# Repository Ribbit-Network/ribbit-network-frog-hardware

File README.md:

# Ribbit Network Frog Sensor
<!-- ALL-CONTRIBUTORS-BADGE:START - Do not remove or modify this section -->

<!-- ALL-CONTRIBUTORS-BADGE:END -->
[This project will create the world's largest Greenhouse Gas Emissions dataset that will empower anyone to join in the work on climate and provide informed data for climate action.](https://ribbitnetwork.org/)

Ribbit Network is a large network of open-source, low-cost, Greenhouse Gas (CO2 and hopefully other gasses in the future) Detection Sensors. These sensor units will be sold by the Ribbit Network and will upload their data to the cloud, creating the world's most complete Greenhouse Gas dataset.

This repository contains the design files, software, documentation, and assembly instructions for the Frog Sensor.

## Frog Sensors
Our “Frogs” are tiny sensors that you can build and deploy at your own home! It’s a small, 
open-source device that measures the amount of CO2 in the air using a tiny laser.
It's easy to set up and will constantly record valuable scientific data on our climate.

Frogs are one of the species that are most affected by climate change! 
Just like our sensors, they ribbit to one another to create a powerful network 
of data about the environment.

## Build a Frog!
We encourage you to jump in and build your own Frog Sensor! It's recommended
to build a V4 Frog and the instructions from this repo are rendered into a nice webpage at the link below:

[Build a Frog Sensor!](https://ribbit-network.github.io/ribbit-network-frog-hardware/)

There have been four major versions of the Frog Sensor to date. We currently recommend building version 4 of the Frog and this repo contains the files and instructions relevant to V4.

* Frog Sensor Version 4 - This version of the sensor is based on an esp32 microcontroller.
* [Frog Sensor Version 3](https://github.com/Ribbit-Network/ribbit-network-frog-hardware/tree/hw_v3) - This version is based on a Raspberry Pi CM4 and includes a fully 3D printed enclosure.
* [Frog Sensor Version 2](https://github.com/Ribbit-Network/ribbit-network-frog-hardware/tree/hw_v2) - This version is based on a Beaglebone black and includes a fully 3D printed enclosure.
* [Frog Sensor Version 1](https://github.com/Ribbit-Network/ribbit-network-frog-hardware/tree/hw_v1) - This version was based on the Raspberry Pi and included an off-the-shelf enclosure

See each folder linked above for the relevant design files, CAD, and assembly instructions!

## Need Help?
[If you are not sure where to start or just want to chat join our developer slack here.](https://join.slack.com/t/ribbitnetworkgroup/shared_invite/zt-2vxvbo7ld-S36SgfDiev~ZQ2zvp03FOg). You can also [start a discussion](https://github.com/Ribbit-Network/ribbit-network-frog-sensor/discussions) right here in Github.

# View the Data!
The first prototype sensors are up and running! [Here is some real data from our sensor network!](https://dashboard.ribbitnetwork.org/) (Note this dashboard is still experimental and may be down occasionally).

[See more about the cloud database here.](https://github.com/Ribbit-Network/ribbit-network-dashboard)

## Questions?
[Check out the Frequently Asked Questions section.](https://github.com/Ribbit-Network/ribbit-network-faq) If you don't see your question, let us know either in a Github Discussion or via chat.

## Ribbit Frog V4
This is the hardware repository that contains all the design files for the physical assembly of the Frog Sensor.

## Bill of Materials (Parts List)
The hardware [Bill of Materials is located here.](ribbit_network_frog_sensor_bom.csv)

## Mechanical CAD Files
The mechanical design files are hosted on Onshape. Onshape is available to use for free with public assemblies and you can create a copy of the assembly for any edits you would like to make.

[Link to Onshape Assembly](https://cad.onshape.com/documents/b3e6eeabf50d585d20f25fc6/w/a4a82302d129f025f23b244a/e/c221edb50cd05a98d22970e2?renderMode=0&uiState=64a86ef7086f6a55cf1984e7)

## Electronics Block Diagram

The diagram above can be edited with drawio or with the awesome [Draw.io Visual Studio Code Plugin](https://marketplace.visualstudio.com/items?itemName=hediet.vscode-drawio)

## Get Involved
Are you interested in getting more involved or leading an effort in the Ribbit Network project? We are recruiting for additional members to join the Core Team. [See the Open Roles and descriptions here.](https://ribbitnetwork.notion.site/Core-Team-Role-Postings-105df298e0634f179f8f063c01708069).

## Contributing
See the [Issues](https://github.com/keenanjohnson/ghg-gas-cloud/issues) section of this project for the work that I've currently scoped out to be done. Reach out to me if you are interested in helping out! The [projects section](https://github.com/Ribbit-Network/ribbit-network-frog-sensor/projects) helps detail the major efforts going on right now.

We have a [contributing guide](https://github.com/Ribbit-Network/ribbit-network-frog-sensor/blob/main/CONTRIBUTING.md) that details the process for making a contribution.

[If you are not sure where to start or just want to chat join our developer slack here.](https://join.slack.com/t/ribbitnetworkgroup/shared_invite/zt-2vxvbo7ld-S36SgfDiev~ZQ2zvp03FOg). You can also [start a discussion](https://github.com/Ribbit-Network/ribbit-network-frog-sensor/discussions) right here in Github.

## Background Information
[See the Wiki for background research.](https://ribbitnetwork.notion.site/Learnings-Low-cost-sensors-for-the-measurement-of-atmospheric-composition-e3d41736c49e41ad81dcdf7e16a6573b) This project is inspired by some awesome research by incredible scientists in academia.

## Ribbit Network
Ribbit Network is a non-profit (501c3) creating the world's largest Greenhouse Gas Emissions dataset that will empower anyone to join in the work on climate and provide informed data for climate action. We're an all volunteer team building everything we do in the open-source community.

If you would like to consider sponsoring Ribbit Network you can do [via this link](https://givebutter.com/ribbitnetwork). The money is used to pay for software fees, purchase R&D hardware and generally support the mission of Ribbit Network.

## Ribbit Network Code of Conduct
By participating in this project, you agree to follow the <a href="https://ribbitnetwork.notion.site/Ribbit-Network-Code-of-Conduct-and-anti-harassment-policy-cc998ef83e7d4ae7abc95508ee6f2b0d">Ribbit Network Code of Conduct and Anti-Harassement Policy</a>.
Violations can be reported anonymously by filling out this <a href="https://docs.google.com/forms/d/e/1FAIpQLSemQSAER8az1lNGoWkL1udsv6O8oPc1WQ3dvQ0b9fJSSMeetQ/viewform">form</a>. 

## Contributors ✨

Thanks goes to these wonderful people ([emoji key](https://allcontributors.org/docs/en/emoji-key)):

<!-- ALL-CONTRIBUTORS-LIST:START - Do not remove or modify this section -->
<!-- prettier-ignore-start -->
<!-- markdownlint-disable -->
<table>
  <tbody>
    <tr>
      <td align="center"><a href="https://www.linkedin.com/in/ericaudiffred/"><br /><sub><b>Eric Audiffred</b></sub></a><br /><a href="#design-eaudiffred" title="Design">🎨</a> <a href="#ideas-eaudiffred" title="Ideas, Planning, & Feedback">🤔</a> <a href="https://github.com/Ribbit-Network/ribbit-network-frog-hardware/commits?author=eaudiffred" title="Tests">⚠️</a></td>
      <td align="center"><a href="https://github.com/djgood"><br /><sub><b>Desmond Good</b></sub></a><br /><a href="#ideas-djgood" title="Ideas, Planning, & Feedback">🤔</a> <a href="https://github.com/Ribbit-Network/ribbit-network-frog-hardware/commits?author=djgood" title="Code">💻</a> <a href="#projectManagement-djgood" title="Project Management">📆</a></td>
      <td align="center"><a href="http://laurencewatson.com"><br /><sub><b>Laurence Watson</b></sub></a><br /><a href="https://github.com/Ribbit-Network/ribbit-network-frog-hardware/commits?author=Rabscuttler" title="Tests">⚠️</a> <a href="https://github.com/Ribbit-Network/ribbit-network-frog-hardware/commits?author=Rabscuttler" title="Documentation">📖</a> <a href="#ideas-Rabscuttler" title="Ideas, Planning, & Feedback">🤔</a> <a href="#projectManagement-Rabscuttler" title="Project Management">📆</a></td>
      <td align="center"><a href="https://spestana.github.io/"><br /><sub><b>Steven Pestana</b></sub></a><br /><a href="https://github.com/Ribbit-Network/ribbit-network-frog-hardware/commits?author=spestana" title="Documentation">📖</a> <a href="#ideas-spestana" title="Ideas, Planning, & Feedback">🤔</a> <a href="#data-spestana" title="Data">🔣</a> <a href="https://github.com/Ribbit-Network/ribbit-network-frog-hardware/commits?author=spestana" title="Tests">⚠️</a> <a href="#financial-spestana" title="Financial">💵</a></td>
      <td align="center"><a href="https://github.com/sanfk2"><br /><sub><b>sanfk2</b></sub></a><br /><a href="https://github.com/Ribbit-Network/ribbit-network-frog-hardware/commits?author=sanfk2" title="Code">💻</a></td>
      <td align="center"><a href="https://github.com/eren-rudy"><br /><sub><b>Eren Rudy</b></sub></a><br /><a href="https://github.com/Ribbit-Network/ribbit-network-frog-hardware/commits?author=eren-rudy" title="Tests">⚠️</a> <a href="https://github.com/Ribbit-Network/ribbit-network-frog-hardware/commits?author=eren-rudy" title="Documentation">📖</a></td>
      <td align="center"><a href="https://github.com/daveb377"><br /><sub><b>David Bengtson</b></sub></a><br /><a href="#ideas-daveb377" title="Ideas, Planning, & Feedback">🤔</a> <a href="#projectManagement-daveb377" title="Project Management">📆</a></td>
    </tr>
    <tr>
      <td align="center"><a href="https://www.linkedin.com/in/lancebantoto/"><br /><sub><b>Lance Bantoto</b></sub></a><br /><a href="#ideas-lwbantoto" title="Ideas, Planning, & Feedback">🤔</a> <a href="#projectManagement-lwbantoto" title="Project Management">📆</a></td>
      <td align="center"><a href="https://github.com/kevinjmiller2"><br /><sub><b>Kevin Miller</b></sub></a><br /><a href="#ideas-kevinjmiller2" title="Ideas, Planning, & Feedback">🤔</a> <a href="#content-kevinjmiller2" title="Content">🖋</a></td>
      <td align="center"><a href="https://balena.io"><br /><sub><b>Marc Pous</b></sub></a><br /><a href="https://github.com/Ribbit-Network/ribbit-network-frog-hardware/commits?author=mpous" title="Tests">⚠️</a></td>
      <td align="center"><a href="https://abesto.net"><br /><sub><b>Zoltán Nagy</b></sub></a><br /><a href="https://github.com/Ribbit-Network/ribbit-network-frog-hardware/commits?author=abesto" title="Code">💻</a></td>
      <td align="center"><a href="https://github.com/eliasfallon"><br /><sub><b>eliasfallon</b></sub></a><br /><a href="https://github.com/Ribbit-Network/ribbit-network-frog-hardware/commits?author=eliasfallon" title="Documentation">📖</a></td>
      <td align="center"><a href="https://github.com/rhampt"><br /><sub><b>Ryan</b></sub></a><br /><a href="https://github.com/Ribbit-Network/ribbit-network-frog-hardware/commits?author=rhampt" title="Documentation">📖</a></td>
      <td align="center"><a href="https://github.com/akhilgupta1093"><br /><sub><b>akhilgupta1093</b></sub></a><br /><a href="https://github.com/Ribbit-Network/ribbit-network-frog-hardware/commits?author=akhilgupta1093" title="Code">💻</a></td>
    </tr>
    <tr>
      <td align="center"><a href="https://github.com/pascaljoly"><br /><sub><b>outdoorclone</b></sub></a><br /><a href="https://github.com/Ribbit-Network/ribbit-network-frog-hardware/commits?author=pascaljoly" title="Documentation">📖</a></td>
      <td align="center"><a href="https://github.com/muditprotect3d"><br /><sub><b>Mudit Agrawal</b></sub></a><br /><a href="#design-muditprotect3d" title="Design">🎨</a></td>
    </tr>
  </tbody>
</table>

<!-- markdownlint-restore -->
<!-- prettier-ignore-end -->

<!-- ALL-CONTRIBUTORS-LIST:END -->

This project follows the [all-contributors](https://github.com/all-contributors/all-contributors) specification. Contributions of any kind welcome!

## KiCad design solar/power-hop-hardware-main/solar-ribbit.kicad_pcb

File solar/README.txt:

# Solar Frog
## Versions
| Solar 1.0 | Desmond’s final submission to Hackster contest. Technically functional and testable, but worth making a few updates before production |
|Solar 1.1|Slightly updated version of Desmond’s submission. Changes include (non-exhaustive):\
- [Bug fix] Updated footprint mapping for Q5|

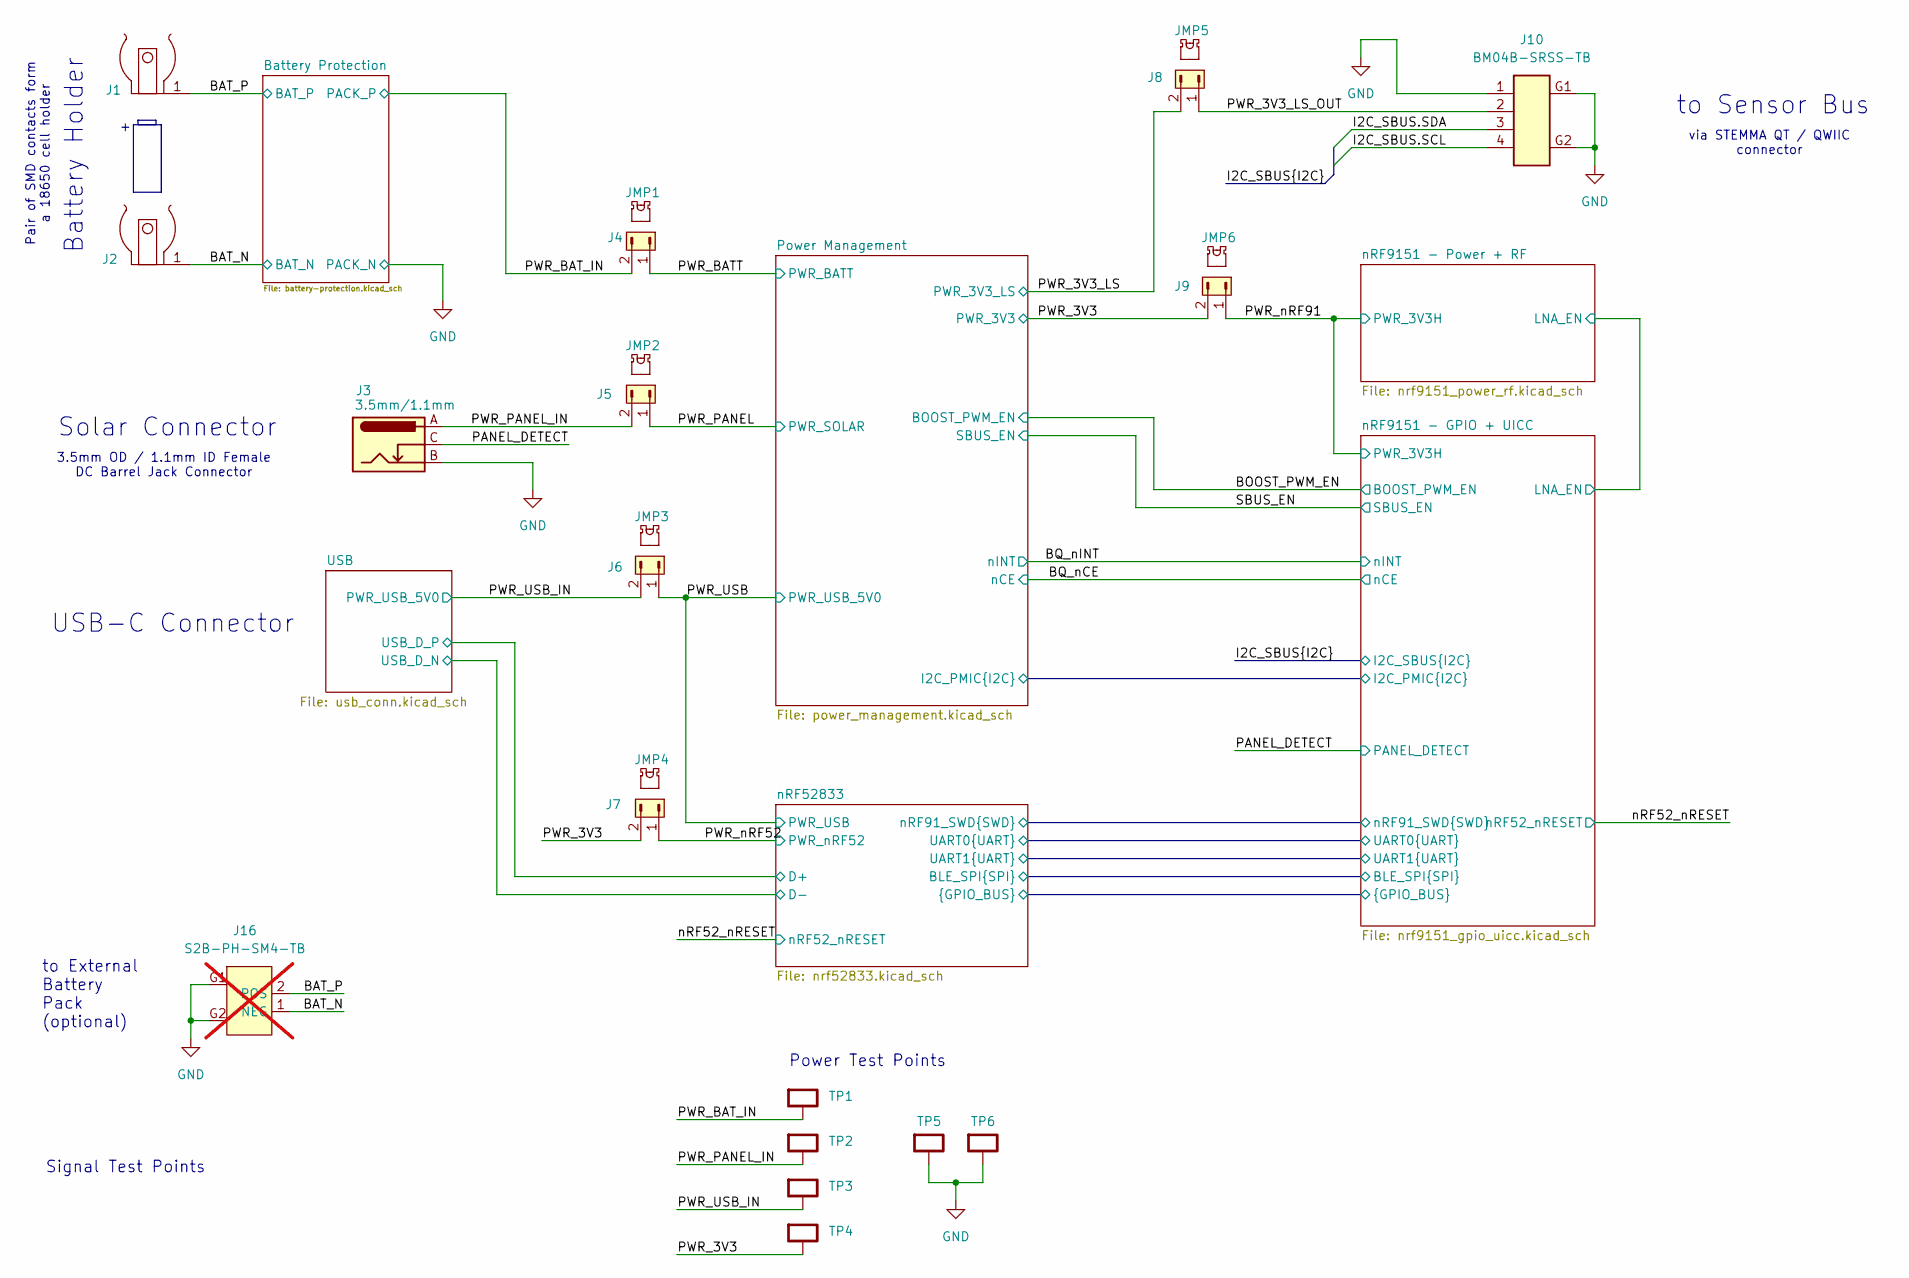
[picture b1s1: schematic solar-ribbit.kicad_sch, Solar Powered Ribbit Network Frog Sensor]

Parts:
J1, J2: KEYSTONE_254; MPN 254
J3: 3.5mm/1.1mm; TENSILITY_54-00125; MPN 54-00125
J4, J5, J6, J7, J8, J9: 10129380-902001BLF; PinHeader_1x02_P2.54mm_Vertical_SMD_Pin1Left; MPN 10129380-902001BLF
J10: BM04B-SRSS-TB; JST_SH_BM04B-SRSS-TB; MPN BM04B-SRSS-TB
J16: S2B-PH-SM4-TB; JST_PH_S2B-PH-SM4-TB_1x02-1MP_P2.00mm_Horizontal; MPN S2B-PH-SM4-TB; not fitted
JMP1, JMP2, JMP3, JMP4, JMP5, JMP6: QPC02SXGN-RC; MPN QPC02SXGN-RC
TP1, TP2, TP3, TP4, TP5, TP6: RCWCTE; KOA_TEST_POINT_1206; MPN RCWCTE

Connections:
/BAT_N: J2.1, J16.1 (NEG); also elsewhere on the board
/BAT_P: J1.1, J16.2 (POS); also elsewhere on the board
/I2C_SBUS.SCL: J10.4; also elsewhere on the board
/I2C_SBUS.SDA: J10.3; also elsewhere on the board
/PANEL_DETECT: J3.C; also elsewhere on the board
/PWR_3V3: J7.2, J9.2, TP4.1; also elsewhere on the board
/PWR_3V3_LS: J8.2; also elsewhere on the board
/PWR_3V3_LS_OUT: J8.1, J10.2
/PWR_BATT: J4.1; also elsewhere on the board
/PWR_BAT_IN: J4.2, TP1.1; also elsewhere on the board
/PWR_PANEL: J5.1; also elsewhere on the board
/PWR_PANEL_IN: J3.A, J5.2, TP2.1
/PWR_USB: J6.1; also elsewhere on the board
/PWR_USB_IN: J6.2, TP3.1; also elsewhere on the board
/PWR_nRF52: J7.1; also elsewhere on the board
/PWR_nRF91: J9.1; also elsewhere on the board
GND: J3.B, J10.1, J10.G1, J10.G2, J16.G1, J16.G2, TP5.1, TP6.1; also elsewhere on the board

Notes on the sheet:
Pair of SMD contacts form a 18650 cell holder
to External Battery Pack (optional)
Battery Holder
via STEMMA QT / QWIIC connector
Solar Connector
to Sensor Bus
Signal Test Points
Power Test Points
3.5mm OD / 1.1mm ID Female DC Barrel Jack Connector
USB-C Connector

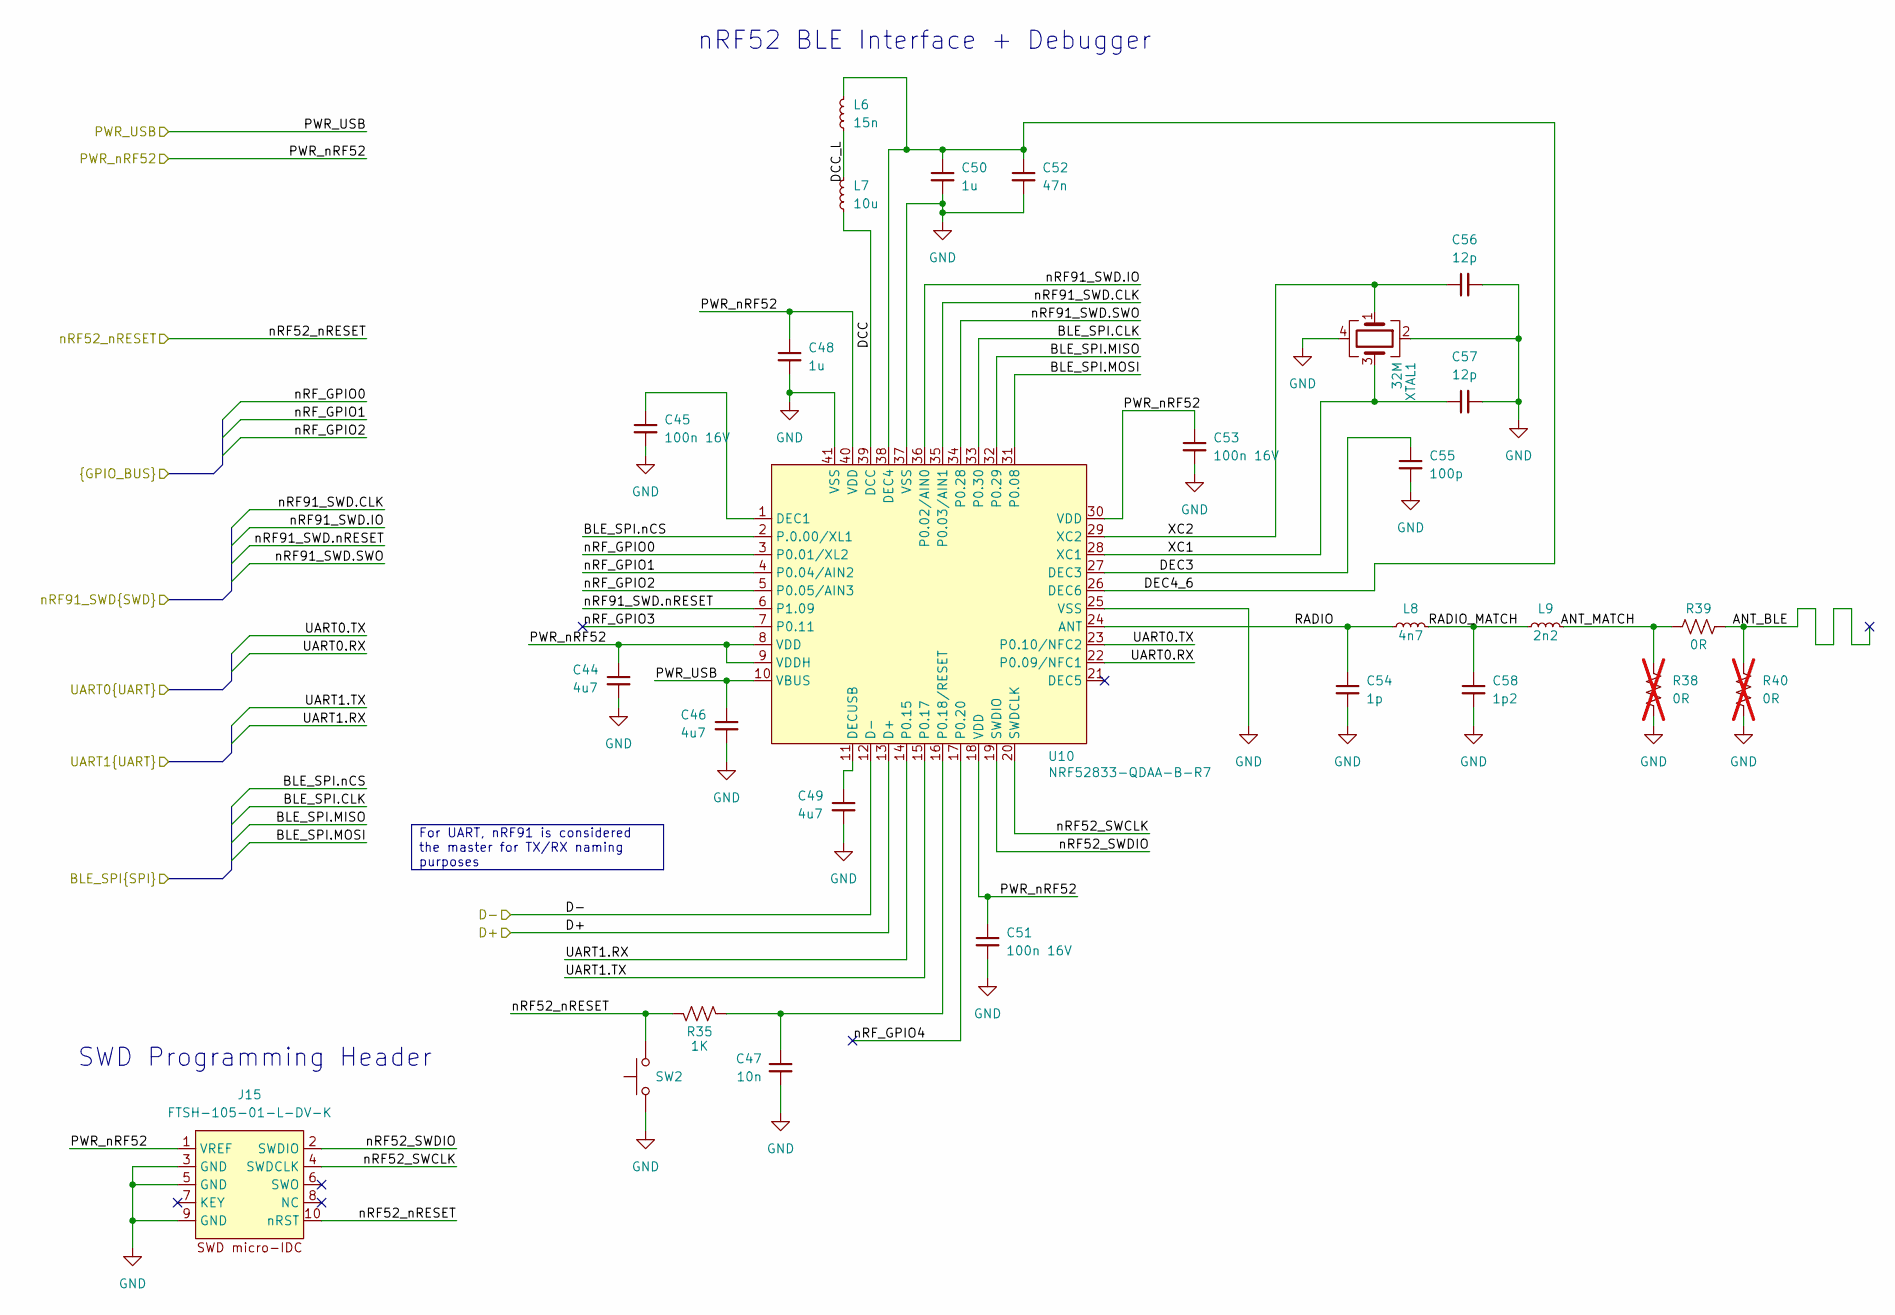
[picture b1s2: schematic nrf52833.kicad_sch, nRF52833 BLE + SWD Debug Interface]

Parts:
C44, C46, C49: 4u7; C_0603_1608Metric; MPN CL10B475KQ8NQNC
C45, C51, C53: 100n 16V; C_0201_0603Metric; MPN GRM033Z71C104KE14J
C47: 10n; C_0402_1005Metric; MPN CC0402KRX7R8BB103
C48, C50: 1u; C_0402_1005Metric; MPN GCM155C71A105KE38D
C52: 47n; C_0201_0603Metric; MPN C0603X7S1A473K030BC
C54: 1p; C_0201_0603Metric; MPN GRM0335C1H1R0WA01D
C55: 100p; C_0201_0603Metric; MPN GRM0335C1H101JA01D
C56, C57: 12p; C_0201_0603Metric; MPN GRM0335C1H120GA01D
C58: 1p2; C_0201_0603Metric; MPN GRM0335C1H1R2WA01D
J15: FTSH-105-01-L-DV-K; SAM_MICRO-IDC_FTSH-105-01-L-DV-K_SMD; MPN FTSH-105-01-L-DV-K
L6: 15n; L_0402_1005Metric; MPN LQG15HS15NJ02D
L7: 10u; L_0603_1608Metric; MPN MLZ1608N100LT000
L8: 4n7; L_0201_0603Metric; MPN LQP03PN4N7J02D
L9: 2n2; L_0201_0603Metric; MPN LQP03TN2N2B02D
R35: 1K; R_0402_1005Metric; MPN ERJ-2RKF1001X
R38, R40: 0R; R_0201_0603Metric; MPN ERJ-1GN0R00C; not fitted
R39: 0R; R_0201_0603Metric; MPN ERJ-1GN0R00C
SW2: PTS636SM50JSMTR LFS; SW_Tactile_SPST_NO_Straight_CK_ PTS636SM50JSMTR LFS; MPN PTS636SM50JSMTR LFS
U10: NRF52833-QDAA-B-R7; QFN-40-1EP_5x5mm_P0.4mm_EP3.6x3.6mm; MPN NRF52833-QDAA-B-R7
XTAL1: 32M; XTAL_MP06003_SMD_2016-4Pin_2.0x1.6mm; MPN MP06003

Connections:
/PWR_USB: C46.1, U10.10 (VBUS); also elsewhere on the board
/PWR_nRF52: C44.1, C48.1, C51.1, C53.1, J15.1 (VREF), U10.8 (VDD), U10.9 (VDDH), U10.18 (VDD), U10.30 (VDD), U10.40 (VDD); also elsewhere on the board
/USB/USB_D_N: U10.12 (D-); also elsewhere on the board
/USB/USB_D_P: U10.13 (D+); also elsewhere on the board
/nRF52_nRESET: J15.10 (nRST), R35.2, SW2.2; also elsewhere on the board
/nRF52833/ANT_BLE: R39.1, R40.1
/nRF52833/ANT_MATCH: L9.2, R38.2, R39.2
/nRF52833/BLE_SPI.CLK: U10.33 (P0.30); also elsewhere on the board
/nRF52833/BLE_SPI.MISO: U10.32 (P0.29); also elsewhere on the board
/nRF52833/BLE_SPI.MOSI: U10.31 (P0.08); also elsewhere on the board
/nRF52833/BLE_SPI.nCS: U10.2 (P.0.00/XL1); also elsewhere on the board
/nRF52833/DCC: L7.1, U10.39 (DCC)
/nRF52833/DCC_L: L6.1, L7.2
/nRF52833/DEC3: C55.1, U10.27 (DEC3)
/nRF52833/DEC4_6: C50.1, C52.1, L6.2, U10.26 (DEC6), U10.38 (DEC4)
/nRF52833/RADIO: C54.1, L8.1, U10.24 (ANT)
/nRF52833/RADIO_MATCH: C58.1, L8.2, L9.1
/nRF52833/UART0.RX: U10.22 (P0.09/NFC1); also elsewhere on the board
/nRF52833/UART0.TX: U10.23 (P0.10/NFC2); also elsewhere on the board
/nRF52833/UART1.RX: U10.14 (P0.15); also elsewhere on the board
/nRF52833/UART1.TX: U10.15 (P0.17); also elsewhere on the board
/nRF52833/XC1: C57.1, U10.28 (XC1), XTAL1.3
/nRF52833/XC2: C56.1, U10.29 (XC2), XTAL1.1
/nRF52833/nRF52_SWCLK: J15.4 (SWDCLK), U10.20 (SWDCLK)
/nRF52833/nRF52_SWDIO: J15.2 (SWDIO), U10.19 (SWDIO)
/nRF52833/nRF91_SWD.CLK: U10.35 (P0.03/AIN1); also elsewhere on the board
/nRF52833/nRF91_SWD.IO: U10.36 (P0.02/AIN0); also elsewhere on the board
/nRF52833/nRF91_SWD.SWO: U10.34 (P0.28); also elsewhere on the board
/nRF52833/nRF91_SWD.nRESET: U10.6 (P1.09); also elsewhere on the board
/nRF52833/nRF_GPIO0: U10.3 (P0.01/XL2); also elsewhere on the board
/nRF52833/nRF_GPIO1: U10.4 (P0.04/AIN2); also elsewhere on the board
/nRF52833/nRF_GPIO2: U10.5 (P0.05/AIN3); also elsewhere on the board
/nRF52833/nRF_GPIO3: U10.7 (P0.11)
/nRF52833/nRF_GPIO4: U10.17 (P0.20)
GND: C44.2, C45.2, C46.2, C47.2, C48.2, C49.2, C50.2, C51.2, C52.2, C53.2, C54.2, C55.2, C56.2, C57.2, C58.2, J15.3 (GND), J15.5 (GND), J15.9 (GND), R38.1, R40.2, SW2.1, U10.25 (VSS), U10.37 (VSS), U10.41 (VSS), XTAL1.2, XTAL1.4; also elsewhere on the board
unnamed: C45.1, U10.1 (DEC1)
unnamed: C49.1, U10.11 (DECUSB)
unnamed: C47.1, R35.1, U10.16 (P0.18/RESET)

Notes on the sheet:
SWD Programming Header
nRF52 BLE Interface + Debugger
For UART, nRF91 is considered the master for TX/RX naming purposes

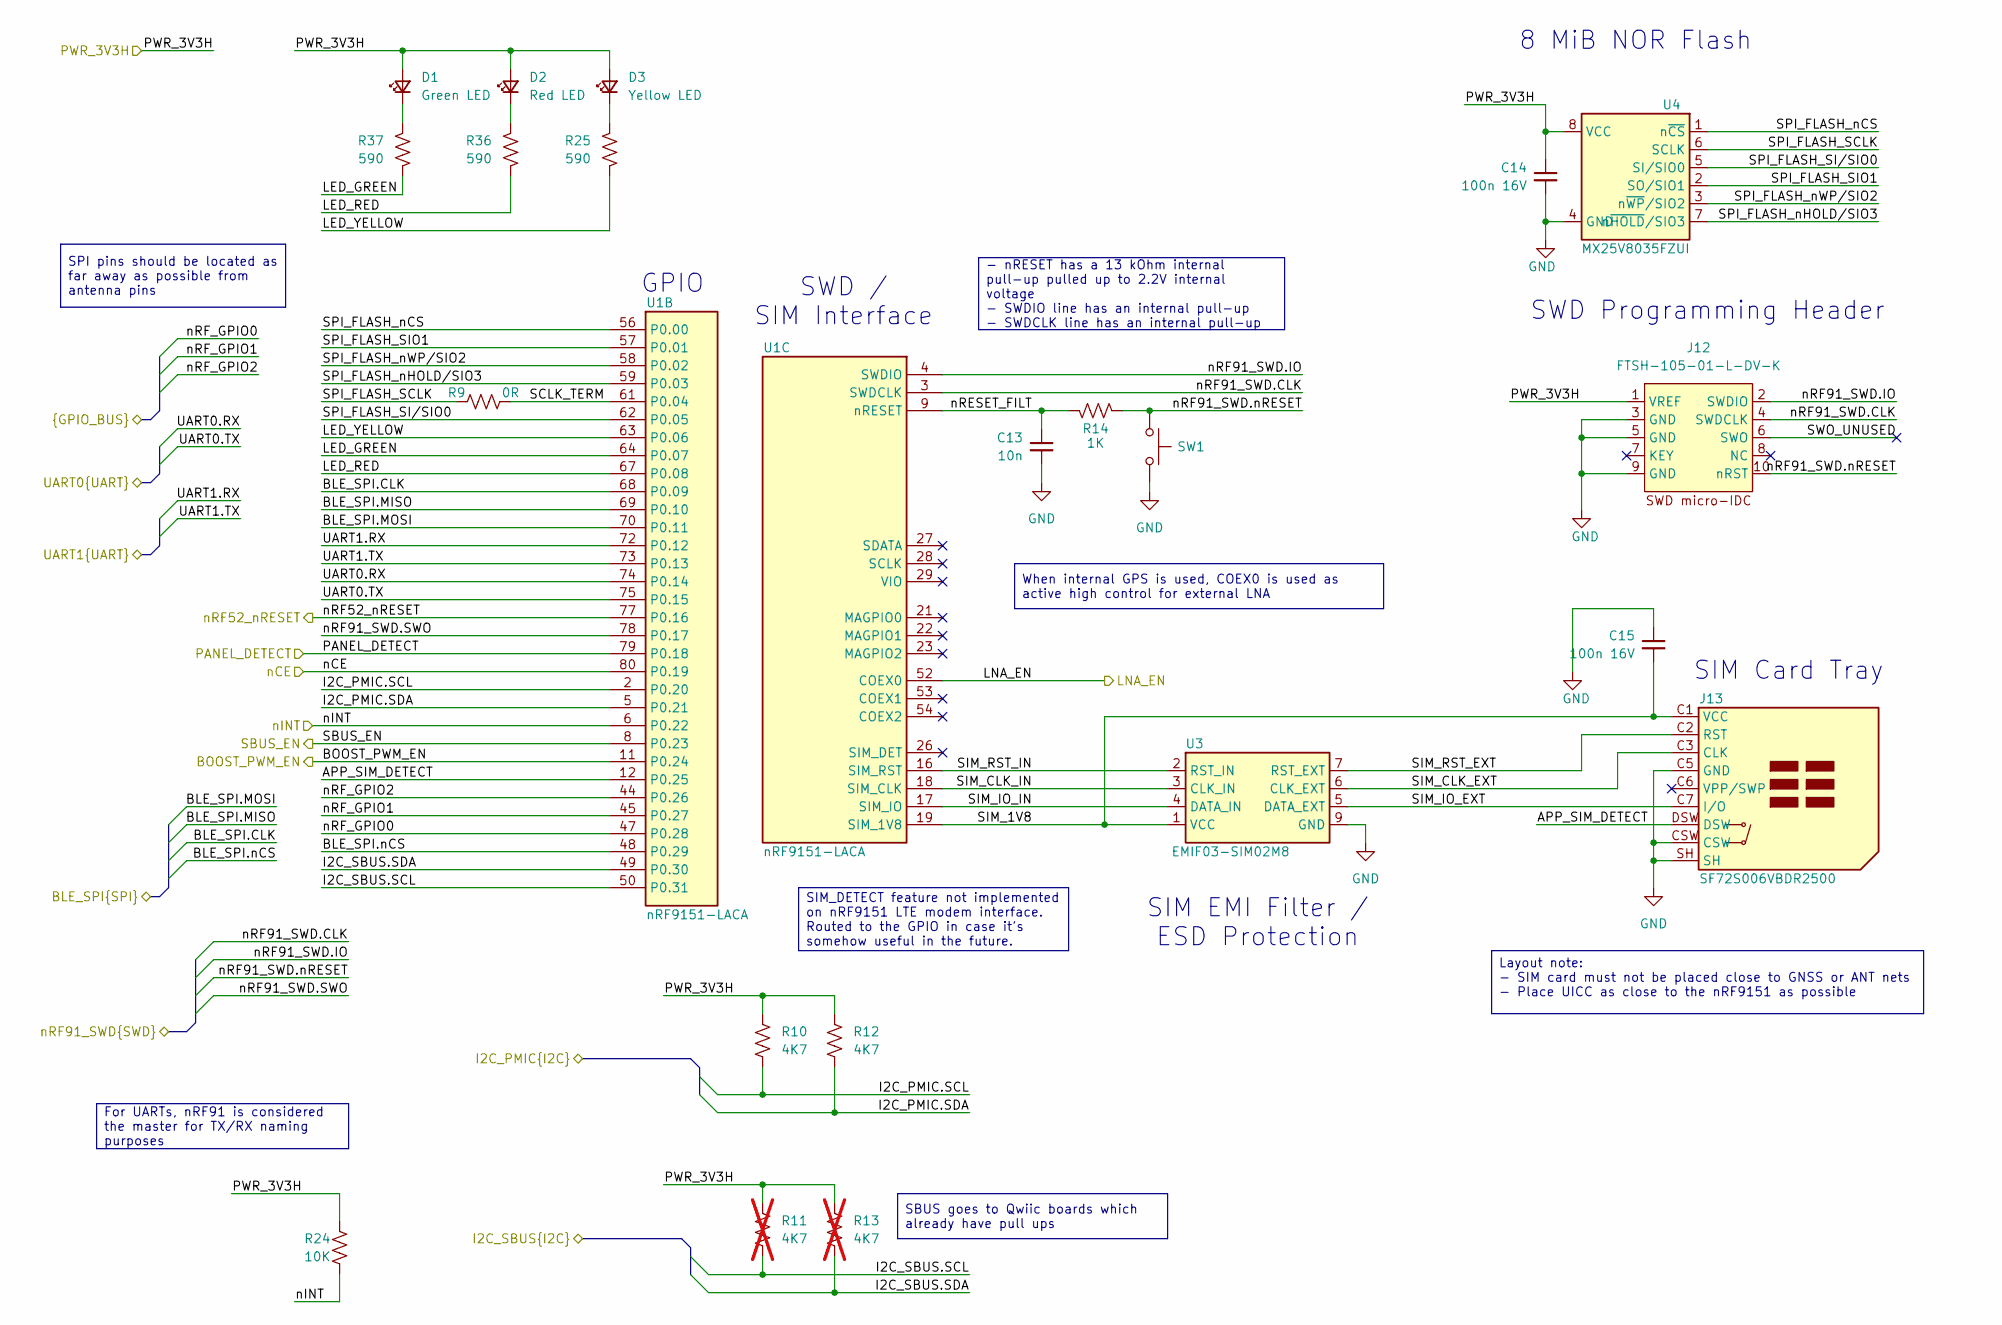
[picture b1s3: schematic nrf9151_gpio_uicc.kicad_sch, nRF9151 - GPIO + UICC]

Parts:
C13: 10n; C_0402_1005Metric; MPN CC0402KRX7R8BB103
C14, C15: 100n 16V; C_0201_0603Metric; MPN GRM033Z71C104KE14J
D1: Green LED; LED_0402_1005Metric; MPN HSMG-C280
D2: Red LED; LED_0402_1005Metric; MPN HSMS-C280
D3: Yellow LED; LED_0402_1005Metric; MPN HSMY-C280
J12: FTSH-105-01-L-DV-K; SAM_MICRO-IDC_FTSH-105-01-L-DV-K_SMD; MPN FTSH-105-01-L-DV-K
J13: SF72S006VBDR2500; JAE_SF72S006VBDR2500; MPN SF72S006VBDR2500
R9: 0R; R_0402_1005Metric; MPN ERJ-2GE0R00X
R10, R12: 4K7; R_0402_1005Metric; MPN ERJ-2RKF4701X
R11, R13: 4K7; R_0402_1005Metric; MPN ERJ-2RKF4701X; not fitted
R14: 1K; R_0402_1005Metric; MPN ERJ-2RKF1001X
R24: 10K; R_0402_1005Metric; MPN ERJ-2RKF1002X
R25, R36, R37: 590; R_0402_1005Metric; MPN ERJ-2RKF5900X
SW1: PTS636SM50JSMTR LFS; SW_Tactile_SPST_NO_Straight_CK_ PTS636SM50JSMTR LFS; MPN PTS636SM50JSMTR LFS
U1: nRF9151-LACA; NORDIC_LGA-113; MPN NRF9151-LACA-R
U3: EMIF03-SIM02M8; ST_UFDFN-8; MPN EMIF03-SIM02M8
U4: MX25V8035FZUI; MX_8USON; MPN MX25V8035FZUI

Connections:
/BOOST_PWM_EN: U1.11 (P0.24); also elsewhere on the board
/BQ_nCE: U1.80 (P0.19); also elsewhere on the board
/BQ_nINT: R24.2, U1.6 (P0.22); also elsewhere on the board
/I2C_SBUS.SCL: R11.2, U1.50 (P0.31); also elsewhere on the board
/I2C_SBUS.SDA: R13.2, U1.49 (P0.30); also elsewhere on the board
/PANEL_DETECT: U1.79 (P0.18); also elsewhere on the board
/PWR_nRF91: C14.1, D1.2 (A), D2.2 (A), D3.2 (A), J12.1 (VREF), R10.1, R11.1, R12.1, R13.1, R24.1, U4.8 (VCC); also elsewhere on the board
/Power Management/I2C_PMIC.SCL: R10.2, U1.2 (P0.20); also elsewhere on the board
/Power Management/I2C_PMIC.SDA: R12.2, U1.5 (P0.21); also elsewhere on the board
/SBUS_EN: U1.8 (P0.23); also elsewhere on the board
/nRF52_nRESET: U1.77 (P0.16); also elsewhere on the board
/nRF9151 - GPIO + UICC/APP_SIM_DETECT: J13.DSW, U1.12 (P0.25)
/nRF9151 - GPIO + UICC/LED_GREEN: R37.2, U1.64 (P0.07)
/nRF9151 - GPIO + UICC/LED_RED: R36.2, U1.67 (P0.08)
/nRF9151 - GPIO + UICC/LED_YELLOW: R25.2, U1.63 (P0.06)
/nRF9151 - GPIO + UICC/LNA_EN: U1.52 (COEX0); also elsewhere on the board
/nRF9151 - GPIO + UICC/SCLK_TERM: R9.2, U1.61 (P0.04)
/nRF9151 - GPIO + UICC/SIM_CLK_EXT: J13.C3 (CLK), U3.6 (CLK_EXT)
/nRF9151 - GPIO + UICC/SIM_CLK_IN: U1.18 (SIM_CLK), U3.3 (CLK_IN)
/nRF9151 - GPIO + UICC/SIM_IO_EXT: J13.C7 (I/O), U3.5 (DATA_EXT)
/nRF9151 - GPIO + UICC/SIM_IO_IN: U1.17 (SIM_IO), U3.4 (DATA_IN)
/nRF9151 - GPIO + UICC/SIM_RST_EXT: J13.C2 (RST), U3.7 (RST_EXT)
/nRF9151 - GPIO + UICC/SIM_RST_IN: U1.16 (SIM_RST), U3.2 (RST_IN)
/nRF9151 - GPIO + UICC/SPI_FLASH_SCLK: R9.1, U4.6 (SCLK)
/nRF9151 - GPIO + UICC/SPI_FLASH_SIO1: U1.57 (P0.01), U4.2 (SO/SIO1)
/nRF9151 - GPIO + UICC/SPI_FLASH_SI/SIO0: U1.62 (P0.05), U4.5 (SI/SIO0)
/nRF9151 - GPIO + UICC/SPI_FLASH_nCS: U1.56 (P0.00), U4.1 (n~CS)
/nRF9151 - GPIO + UICC/SPI_FLASH_nHOLD/SIO3: U1.59 (P0.03), U4.7 (n~HOLD/SIO3)
/nRF9151 - GPIO + UICC/SPI_FLASH_nWP/SIO2: U1.58 (P0.02), U4.3 (n~WP/SIO2)
/nRF9151 - GPIO + UICC/SWO_UNUSED: J12.6 (SWO)
/nRF9151 - GPIO + UICC/nRESET_FILT: C13.1, R14.2, U1.9 (nRESET)
/nRF9151 - Power + RF/GNSS_LNA_RF: U1.42 (GPS); also elsewhere on the board
/nRF9151 - Power + RF/GNSS_RF: U1.37 (AUX); also elsewhere on the board
/nRF9151 - Power + RF/LTE_ANT_TUNED: U1.35 (ANT); also elsewhere on the board
/nRF9151 - Power + RF/nRF91_VDD: U1.14 (VDD); also elsewhere on the board
/nRF9151 - Power + RF/nRF91_VDD_GPIO: U1.65 (VDD_GPIO); also elsewhere on the board
/nRF52833/BLE_SPI.CLK: U1.68 (P0.09); also elsewhere on the board
/nRF52833/BLE_SPI.MISO: U1.69 (P0.10); also elsewhere on the board
/nRF52833/BLE_SPI.MOSI: U1.70 (P0.11); also elsewhere on the board
/nRF52833/BLE_SPI.nCS: U1.48 (P0.29); also elsewhere on the board
/nRF52833/UART0.RX: U1.74 (P0.14); also elsewhere on the board
/nRF52833/UART0.TX: U1.75 (P0.15); also elsewhere on the board
/nRF52833/UART1.RX: U1.72 (P0.12); also elsewhere on the board
/nRF52833/UART1.TX: U1.73 (P0.13); also elsewhere on the board
/nRF52833/nRF91_SWD.CLK: J12.4 (SWDCLK), U1.3 (SWDCLK); also elsewhere on the board
/nRF52833/nRF91_SWD.IO: J12.2 (SWDIO), U1.4 (SWDIO); also elsewhere on the board
/nRF52833/nRF91_SWD.SWO: U1.78 (P0.17); also elsewhere on the board
/nRF52833/nRF91_SWD.nRESET: J12.10 (nRST), R14.1, SW1.1; also elsewhere on the board
/nRF52833/nRF_GPIO0: U1.47 (P0.28); also elsewhere on the board
/nRF52833/nRF_GPIO1: U1.45 (P0.27); also elsewhere on the board
/nRF52833/nRF_GPIO2: U1.44 (P0.26); also elsewhere on the board
GND: C13.2, C14.2, C15.1, J12.3 (GND), J12.5 (GND), J12.9 (GND), J13.C5 (GND), J13.CSW, J13.SH, SW1.2, U1.1 (GND), U1.7 (GND), U1.13 (GND), U1.15 (GND), U1.20 (GND), U1.25 (GND), U1.30 (GND), U1.34 (GND), U1.36 (GND), U1.38 (GND), U1.39 (GND), U1.40 (GND), U1.41 (GND), U1.43 (GND), U1.46 (GND), U1.51 (GND), U1.55 (GND), U1.60 (GND), U1.66 (GND), U1.71 (GND), U1.76 (GND), U1.105 (GND), U1.106 (GND), U1.107 (GND), U1.108 (GND), U1.109 (GND), U1.110 (GND), U1.111 (GND), U1.112 (GND), U1.113 (GND), U3.9 (GND), U3.GND, U4.4 (GND), U4.GND; also elsewhere on the board
unnamed: D1.1 (K), R37.1
unnamed: D2.1 (K), R36.1
unnamed: D3.1 (K), R25.1
unnamed 124: U1.24 (DEC0); also elsewhere on the board
unnamed 125: U1.10 (ENABLE); also elsewhere on the board
VCC: C15.2, J13.C1 (VCC), U1.19 (SIM_1V8), U3.1 (VCC), U3.8 (VCC)

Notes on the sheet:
SIM EMI Filter / ESD Protection
SIM Card Tray
SWD Programming Header
SWD / SIM Interface
GPIO
8 MiB NOR Flash
For UARTs, nRF91 is considered the master for TX/RX naming purposes
When internal GPS is used, COEX0 is used as active high control for external LNA
SBUS goes to Qwiic boards which already have pull ups
- nRESET has a 13 kOhm internal pull-up pulled up to 2.2V internal voltage - SWDIO line has an internal pull-up - SWDCLK line has an internal pull-up
SPI pins should be located as far away as possible from antenna pins
SIM_DETECT feature not implemented on nRF9151 LTE modem interface. Routed to the GPIO in case it's somehow useful in the future.
Layout note: - SIM card must not be placed close to GNSS or ANT nets - Place UICC as close to the nRF9151 as possible

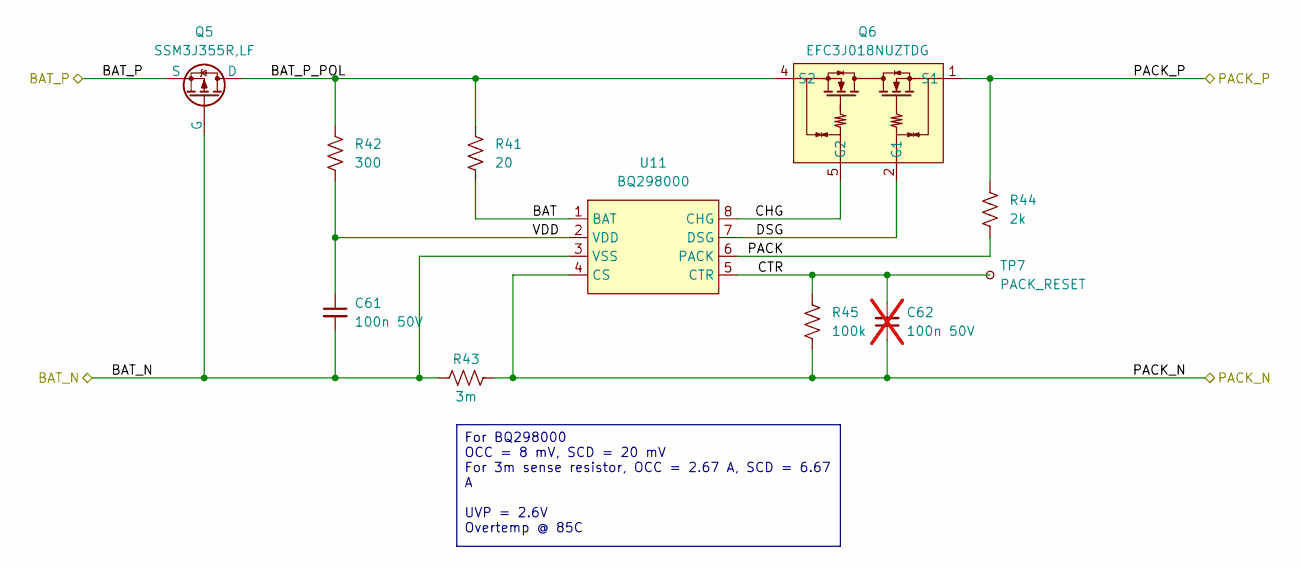
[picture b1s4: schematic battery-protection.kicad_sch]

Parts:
C61: 100n 50V; C_0402_1005Metric; MPN GRM155R71H104KE14D
C62: 100n 50V; C_0402_1005Metric; MPN GRM155R71H104KE14D; not fitted
Q5: SSM3J355R,LF; SOT-23; MPN SSM3J355R,LF
Q6: EFC3J018NUZTDG; ON_6-WLCSP_1.77x3.05; MPN EFC3J018NUZTDG
R41: 20; R_0402_1005Metric; MPN ERJ-2RKF20R0X
R42: 300; R_0402_1005Metric; MPN ERJ-2RKF3000X
R43: 3m; R_0805_2012Metric; MPN PMR10EZPFV3L00
R44: 2k; R_0402_1005Metric; MPN ERJ-2RKF2001X
R45: 100k; R_0402_1005Metric; MPN RC0402FR-07100KL
TP7: PACK_RESET; TestPoint_Pad_1.0x1.0mm; Part-DB ID 144
U11: BQ298000; TI_X2QFN-8; MPN BQ298000RUGT

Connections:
/BAT_N: C61.2, Q5.1 (G), R43.2, U11.3 (VSS); also elsewhere on the board
/BAT_P: Q5.2 (S); also elsewhere on the board
/Battery Protection/BAT: R41.2, U11.1 (BAT)
/Battery Protection/BAT_P_POL: Q5.3 (D), Q6.4 (S2), Q6.6 (S2), R41.1, R42.1
/Battery Protection/CHG: Q6.5 (G2), U11.8 (CHG)
/Battery Protection/CTR: C62.2, R45.1, TP7.1, U11.5 (CTR)
/Battery Protection/DSG: Q6.2 (G1), U11.7 (DSG)
/Battery Protection/PACK: R44.2, U11.6 (PACK)
/Battery Protection/VDD: C61.1, R42.2, U11.2 (VDD)
/PWR_BAT_IN: Q6.1 (S1), Q6.3 (S1), R44.1; also elsewhere on the board
GND: C62.1, R43.1, R45.2, U11.4 (CS); also elsewhere on the board

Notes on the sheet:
For BQ298000 OCC = 8 mV, SCD = 20 mV For 3m sense resistor, OCC = 2.67 A, SCD = 6.67 A UVP = 2.6V Overtemp @ 85C
